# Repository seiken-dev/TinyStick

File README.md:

# TinyStick

**TinyStick**は、**ATtiny3217**(32KB Flash, 2KB SRAM, 256B EEPROM)を搭載した、Arduino互換の開発キットです。消費電流は約4.5mA(クロック10MHz。スリープ時は0.1mA未満)と小さく、コイン電池で長期間動作します。プログラムの書き込みは、付属の**USBシリアル変換基板**(CH340E搭載)で行います。詳しくは、 [tinystick.jp](https://www.tinystick.jp)をご覧ください。

# コンテンツ
- **Arduino**<br>
PlatformIOでビルドできるデモのソースコードです。
- **KiCad**<br>
[KiCad](https://www.kicad.org/)(7.0)のプロジェクトです。TinyStick本体の**TS_Core.kicad_pro**と、USBシリアル変換基板の**TS_USB.kicad_pro**が含まれます。
- **schematic**<br>
TinyStick本体とUSBシリアル変換基板の回路図PDFです。
- **Blender**<br>
3Dプリントケース作成用のBlenderのプロジェクトファイルと、発注に使用したSTLファイルです。

# プログラミング
**TinyStick**のプログラミングは、[PlatformIO](https://platformio.org/)で行います。[Arduino IDE](https://www.arduino.cc/en/software)は、2.3版ではTinyAVR用のボードマネージャーの定義が読み込めない等の理由で推奨しません。(→[参考](https://ameblo.jp/pta55/entry-12835016734.html))

### ビルド
- **PlatformIO**のプロジェクトフォルダに**Arduino**以下をコピーし、適当な名前(例:TinyStickDemo)に変更します。
- **PlatformIO**の**Home**画面から[**Open Project...**]で、このプロジェクトを開きます。
- 必要なplatform(**Atmel megaAVR**)のインストールが自動的に始まります。
- インストールが完了したら**Build**してください。

### UPDI書き込み
- USBシリアル変換基板をUSBケーブルで接続して、スイッチをオンします(赤いLEDが光ります)。このとき、ドライバを自動認識しない場合は、[メーカーのHP](https://wch-ic.com/search?q=CH340&t=downloads)からCH340のドライバをダウンロードしてインストールしてください。
- Windowsの場合は、デバイスマネージャの「ポート(COMとLPT)」に「USB-SERIAL CH340 (COMxx)」と表示されれば完了です。
- **PlatformIO**の**Upload**をクリックすると、プログラムを転送します。

### シリアルデバッグ
- 横のボタン(**Button5**)を押して「Bounce Ball」デモに切り替えたあと、**PlatformIO**の**Serial Monitor**または**Tera Term**等のターミナルアプリを起動すると、加速度の数値が流れてきます。
- このUSBシリアル変換基板は、ターミナルアプリを起動するとRTS信号がLOWになることを利用して、UPDI書き込みとシリアル通信モードを自動的に切り替えます。(Windowsで確認 →[参考](https://ehbtj.com/electronics/make-serial-updi-programmer/))

### platformio.ini
プロジェクトのルートにある設定ファイルです。重要な項目について説明します。

`board_build.f_cpu = 10000000`<br>
CPUクロックを設定します。初期値は10MHz、最大は20MHzです。必ず5の倍数にしてください。そうしないとシリアル通信が文字化けします。また5MHzにすると、I2Cが正常に動作しません。記述しないと16MHzになります。

### ソースコード
- **main.cpp**<br>
メインプログラムで、初期化、タイトル表示、サイドボタン(**Button5**)によるデモの切り替え、長押しによるバックライトのオンオフを処理します。

- **TinyStickDef.h**<br>
共通の#define、ピン定義です。

- **TinyStick.h .cpp**<br>
ボタン、圧電ブザーのクラス、スリープ関連のグローバル関数です。

- **TinyLCD.h .cpp**<br>
バックライト付きLCD [**AQM1248A**](https://akizukidenshi.com/catalog/g/g110048/)に、ビットマップまたは文字を表示するクラスです。文字は、拡大・ボールド・白黒反転・縦・プロポーショナル表示に対応しています。

- **font8x8.h**<br>
8x8ドットフォントです。0x20から0x7Fまでの英数記号です。

- **TinyApp.h .cpp**<br>
複数のアプリを切り替えるときは、このクラスの派生クラスを作成して**main.cpp**に定義するだけで、サイドボタン(**Button5**)で切り替えられます。

- **I2Cbase.h .cpp**<br>
本体内蔵の加速度センサ(**LIS2DH12**)と、M5StickC用のENV Hat(**SHT30**)の基底クラスです。

- **octave.h**<br>
ドレミの周波数を定義したファイルです。

- **playDigit.h .cpp**<br>
２桁の整数値をドレミの音程で鳴らす関数です。

- **app/**<br>
6つのデモアプリです。**TinyApp**の派生クラスです。
  - **EnvHat.h .cpp**<br>
  **ENV Hat**で温度/湿度を表示します。**Button1**で次のアプリに切り替えます。装着されていないときはスキップします。

  - **KitchenTimer.h .cpp**<br>
  キッチンタイマーです。最大99分。スタートすると、分をEEPROMに保存します。

  - **AccelDemo.h .cpp**<br>
  加速度センサのデモです。傾けると玉が転がります。

  - **FontTest.h .cpp**<br>
  8x8ドットフォントをダンプします。**Button1**で拡大、**Button2,3**でスクロールします。

  - **Tetris.h .cpp**<br>
  お馴染みのゲームで、縦向きで遊びます。

  - **Maze3D.h .cpp**<br>
  Line関数を利用した3次元迷路です。

### スリープ機能
一定時間のスリープが出来ます。いずれかのボタンを押すと、スリープから復帰します。
- 時間は任意の時間ではなく、**TinyStick.h**の`enum SleepTime`の時間しか設定できません。
- 本来PX2,PX6ピンに接続されたボタン(TinyStickではButton1のみ)でしかスリープからの復帰はできませんが、これは**FALLING**モードの場合で、**LOW**モードならどのボタンでも復帰が可能です。このため、**LOW**モードでスリープし、起きたら**FALLING**モードに変更して、連続して割り込みが入らないようにしています。

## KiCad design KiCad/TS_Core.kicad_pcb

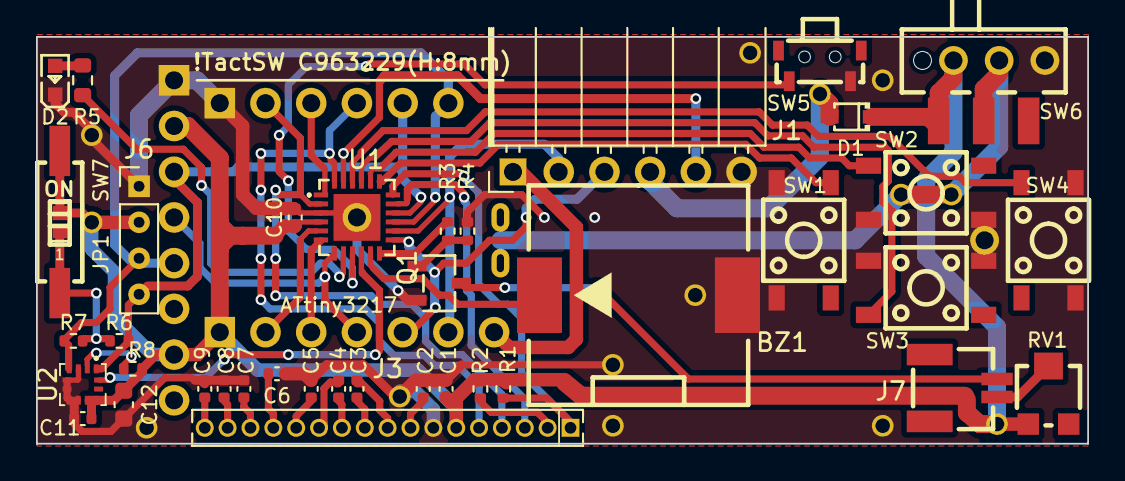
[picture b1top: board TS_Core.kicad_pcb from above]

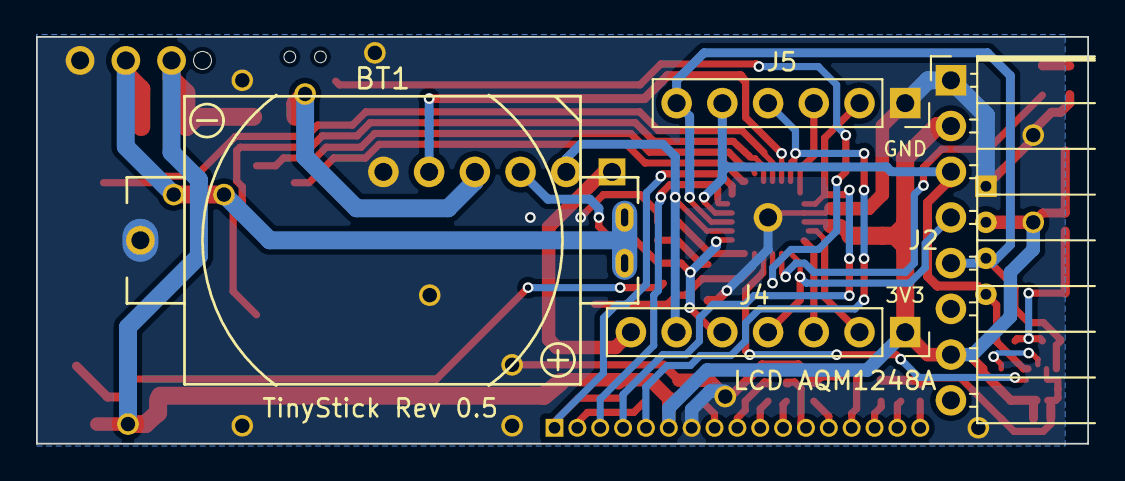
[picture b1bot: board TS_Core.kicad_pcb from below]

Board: 2 copper layers, 58.4 x 22.6 mm, 43 parts (4 on the bottom side), 44 nets.

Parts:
BT1: CR2032; BAT-CR2032-2
BZ1: PKLCS1212E2000; BUZ-SMD_2P-L12.0-W12.0-L
C1, C2, C3, C4, C5, C6, C7, C8, C9: 1u; C_0402_1005Metric
C10, C11: 0.1u; C_0402_1005Metric
C12: 10u; C_0603_1608Metric
D1: 1N5819WS; SOD-323_L1.8-W1.3-LS2.5-RD
D2: SML-D12P8WT86; LED0603-RD_GREEN
J1: USB Serial
J2: M5StickC Hat; PinSocket_M5StickHat
J3: AQM1248A
J4: TinyStick_Ext1; PinSocket_1x07_P2.54mm_Vertical
J5: TinyStick_Ext2; PinSocket_1x06_P2.54mm_Vertical
J6: Grove Connector; Grove_Connector
J7: LCD BackLight; CONN-SMD_HC-1.0-2PWT
JP1: SolderJumper_2_Open; SolderJumper-2_Open_mini
Q1: AO3400A
R1, R2, R6, R7, R8: 10K; R_0402_1005Metric
R3: 20K; R_0402_1005Metric
R4: 100K; R_0402_1005Metric
R5: 470; R_0603_1608Metric
RV1: 2K; RES-ADJ-SMD_G32AT
SW1, SW2, SW3, SW4: Tactile; SW-SMD_4P-L4.5-W4.5-P3.00-LS7.5
SW5: Tactile(Side); SW-SMD_BZCN_TSA002A35
SW6: Slide; SW-SMD_K3-1280S-K1
SW7: DIP; SW-SMD_TSD101EZ
U1: ATtiny3217; HVQFN-24_L4.0-W4.0-P0.50
U2: LIS2DH12; LGA-12_L2.0-W2.0-P0.50-BL

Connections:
+3V3: C1.1, C10.1, C11.1, C12.1, D1.1 (K), J2.2 (5V), J2.7 (3V3), J3.6 (VDD), J4.1, J6.2 (VCC), JP1.2 (B), R1.1, R2.1, R8.1, RV1.3, SW6.1 (A), SW7.2, U1.4 (VCC), U2.9 (Vdd), U2.10 (Vdd_IO)
+5V: J1.1 (+5V), J4.7
Buz: BZ1.1 (-), U1.11 (PB5)
GND: BT1.2 (-), BZ1.2 (+), C1.2, C2.1, C5.1, C6.1, C7.1, C8.1, C9.1, C10.2, C11.2, C12.2, D2.1 (K), J1.6 (GND), J2.1 (GND), J3.7 (VSS), J5.1, J6.1 (GND), Q1.2 (S), R4.2, SW1.3, SW1.4, SW2.3, SW2.4, SW3.3, SW3.4, SW4.3, SW4.4, SW5.2, U1.3 (GND), U1.25 (EP), U2.3 (SA0), U2.5 (RES), U2.6 (GND), U2.7 (GND), U2.8 (GND)
LCD_BL: R3.1, U1.12 (PB4)
LCD_CS: J3.1 (/CS1B), R1.2, U1.18 (PC1)
LCD_RS: J3.3 (RS), U1.17 (PC0)
LED: R5.1, U1.8 (PA7)
MISO: J5.3, U1.1 (PA2/MISO)
MOSI: J3.5 (SDA), J5.4, U1.24 (PA1/MOSI)
unnamed: BT1.1 (+), SW6.2 (B)
unnamed: D1.2 (A), J1.4 (3V3)
unnamed: D2.2 (A), R5.2
unnamed: C3.2, J3.10 (C1+)
unnamed: C3.1, J3.9 (C1-)
unnamed: C4.2, J3.11 (C2+)
unnamed: C4.1, J3.12 (C2-)
unnamed: C9.2, J3.17 (V0)
unnamed: C5.2, J3.13 (V1)
unnamed: C6.2, J3.14 (V2)
unnamed: C7.2, J3.15 (V3)
unnamed: C8.2, J3.16 (V4)
unnamed: C2.2, J3.8 (VOUT)
unnamed: J3.2 (/RST), R2.2
unnamed: J7.1 (LCD_BL_A), RV1.2
unnamed: J7.2 (LCD_BL_K), Q1.3 (D)
unnamed: JP1.1 (A), R6.1, R7.1, SW7.1
unnamed: Q1.1 (G), R3.2, R4.1
unnamed: R8.2, U2.2 (CS)
PA4: J4.2, U1.5 (PA4/SS)
PA5: J4.3, U1.6 (PA5)
PA6: J2.4 (G36/G25), J4.4, U1.7 (PA6)
PB6: U1.10 (PB6), U2.12 (INT1)
RXD: J1.3 (TXD), J4.5, U1.13 (PB3/RXD)
SCK: J3.4 (SCL), J5.2, U1.2 (PA3/SCK)
SCL: J2.3 (G26), J5.5, J6.4 (SCL), R6.2, U1.16 (PB0/SCL), U2.1 (SCL)
SDA: J2.5 (G0), J5.6, J6.3 (SDA), R7.2, U1.15 (PB1/SDA), U2.4 (SDA)
SW1: SW1.1, SW1.2, U1.19 (PC2)
SW2: SW2.1, SW2.2, U1.20 (PC3)
SW3: SW3.1, SW3.2, U1.21 (PC4)
SW4: SW4.1, SW4.2, U1.22 (PC5)
SW5: SW5.1, U1.9 (PB7)
TXD: J1.2 (RXD), J4.6, U1.14 (PB2/TXD)
UPDI: J1.5 (UPDI), U1.23 (PA0/UPDI)

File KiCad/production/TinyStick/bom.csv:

Designator,Footprint,Quantity,Value,LCSC Part #
"_16, _15, _14, _13, _12, _11, _10, _9, _8, _7, _6, _5, _4, _3, _2, ",,16,,
BT1,BAT-CR2032-2,1,CR2032,
BZ1,BUZ-SMD_2P-L12.0-W12.0-L,1,PKLCS1212E2000,C184513
"C1, C2, C3, C4, C5, C6, C7, C8, C9",0402,9,1u,C52923
"C10, C11",0402,2,0.1u,C1525
C12,0603,1,10u,C19702
D1,SOD-323_L1.8-W1.3-LS2.5-RD,1,1N5819WS,C191023
D2,LED0603-RD_GREEN,1,SML-D12P8WT86,C510026
J3,AQM1248A,1,AQM1248A,
J4,PinSocket_1x07_P2.54mm_Vertical,1,TinyStick_Ext1,
J5,PinSocket_1x06_P2.54mm_Vertical,1,TinyStick_Ext2,
J6,Grove_Connector,1,Grove Connector,
J7,CONN-SMD_HC-1.0-2PWT,1,LCD BackLight,C2845361
JP1,SolderJumper-2_Open_mini,1,SolderJumper_2_Open,
Q1,AO3400A,1,AO3400A,C20917
"R1, R2, R6, R7, R8",0402,5,10K,C25744
R3,0402,1,20K,C25765
R4,0402,1,100K,C25741
R5,0603,1,470,C23179
RV1,RES-ADJ-SMD_G32AT,1,2K,C128118
"SW1, SW2, SW3, SW4",SW-SMD_4P-L4.5-W4.5-P3.00-LS7.5,4,Tactile,C963229
SW5,SW-SMD_BZCN_TSA002A35,1,Tactile(Side),C2846757
SW6,SW-SMD_K3-1280S-K1,1,Slide,C128953
SW7,SW-SMD_TSD101EZ,1,DIP,C2758180
U1,HVQFN-24_L4.0-W4.0-P0.50,1,ATtiny3217,C1340454
U2,LGA-12_L2.0-W2.0-P0.50-BL,1,LIS2DH12,C110926

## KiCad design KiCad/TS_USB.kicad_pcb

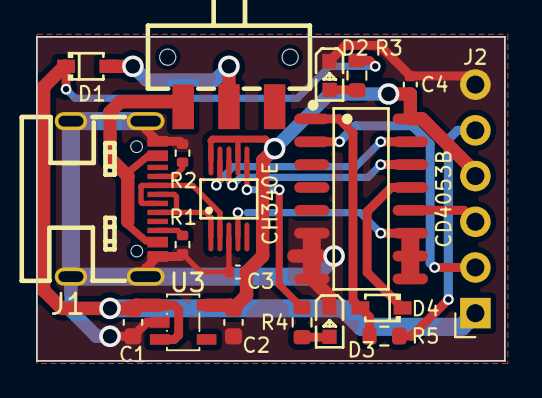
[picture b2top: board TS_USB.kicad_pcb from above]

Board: 2 copper layers, 26.0 x 18.0 mm, 19 parts (0 on the bottom side), 20 nets.

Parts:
C1, C2: 10u; C_0603_1608Metric
C3, C4: 0.1u; C_0402_1005Metric
CD4053B: CD4053B; SOIC-16_L9.9-W3.9-P1.27-LS6.0
CH340E: CH340E; MSOP-10_L3.0-W3.0-P0.50-LS5.0
D1: NSR0320MW2T1G; SOD-323_L1.8-W1.3-LS2.5-RD
D2, D3: LED; LED0603-RD_GREEN
D4: 1N5819WS; SOD-323_L1.8-W1.3-LS2.5-RD
J1: USB_C_Receptacle_USB2.0; USB-C-SMD_TYPE-C-16P-1
J2: Conn_01x06_Pin; PinHeader_1x06_P2.54mm
R1, R2: 5.1K; R_0402_1005Metric
R3: 2.7K; R_0603_1608Metric
R4, R5: 470; R_0603_1608Metric
SW1: Slide; SW-SMD_SSSS211603
U3: ME6217C33; SOT-23-5_L3.0-W1.7-P0.95-LS2.8

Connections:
+3V3: C2.1, C3.1, C4.1, CD4053B.16 (VDD), CH340E.7 (VCC), CH340E.10 (V3), J2.4 (3V3), U3.5 (VOUT)
+5V: C1.1, D1.1 (K), J2.1 (+5V), R3.1, U3.1 (VIN), U3.3 (CE)
GND: C1.2, C2.2, C3.2, C4.2, CD4053B.6 (INH), CD4053B.7 (VEE), CD4053B.8 (VSS), CH340E.3 (GND), D2.1 (K), D3.1 (K), J1.A1B12 (GND), J1.B1A12 (GND), J1.EP, J2.6 (GND), R1.2, R2.2, U3.2 (GND)
unnamed: D1.2 (A), SW1.2 (B)
unnamed: D2.2 (A), R3.2
unnamed: D3.2 (A), R4.2
unnamed: CD4053B.1 (b1), D4.2 (A), R5.2
unnamed: CD4053B.13 (a1), D4.1 (K)
unnamed: J1.A5 (CC1), R2.1
unnamed: J1.B5 (CC2), R1.1
unnamed: CD4053B.2 (b0), J2.2 (RXD)
unnamed: CD4053B.12 (a0), J2.3 (TXD)
unnamed: J2.5 (UPDI), R5.1
unnamed: J1.A4B9 (VBUS), J1.B4A9 (VBUS), SW1.1 (A)
unnamed: CD4053B.15 (B), CH340E.9 (RXD)
unnamed: CH340E.6 (TNOW), R4.1
unnamed: CD4053B.14 (A), CH340E.8 (TXD)
unnamed: CH340E.1 (UD+), J1.A6 (D+), J1.B6 (D+)
unnamed: CH340E.2 (UD-), J1.A7 (D-), J1.B7 (D-)
unnamed: CD4053B.9 (SC), CD4053B.10 (SB), CD4053B.11 (SA), CH340E.4 (~RTS)

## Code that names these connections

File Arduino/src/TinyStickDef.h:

#pragma once

#define DEBUG_SERIAL

#define BUTTONS_COUNT 5

#define TS_SLEEP // sleep support
#define LCD_VERTICAL // vertical mode
#define LCD_TEXT_PROP // proportional
#define LCD_DRAW_LINE

//#define PLAY_DIGIT // play digit by tone
#define USE_EEPROM // save settings in EEPROM

#define EEPROM_KITCHEN_TIMER_MINUTE 1

#define PIN_LED PIN_PA7
#define PIN_BUZZER PIN_PB5

#define PIN_LCD_RS PIN_PC0
#define PIN_LCD_CS PIN_PC1
#define PIN_LCD_BL PIN_PB4

#define PIN_BUTTON1 PIN_PC2
#define PIN_BUTTON2 PIN_PC3
#ifdef ARDUINO_attinyxy7
  #define PIN_BUTTON3 PIN_PC4
  #define PIN_BUTTON4 PIN_PC5
#else
  #define PIN_BUTTON3 PIN_PB4
  #define PIN_BUTTON4 PIN_PB5
#endif

#if (BUTTONS_COUNT == 5)
  #define btnSide btn5
  #ifdef ARDUINO_attinyxy7
    #define PIN_BUTTON5 PIN_PB7
  #else
    #define PIN_BUTTON5 PIN_PA5
  #endif
#else
  #define btnSide btn4
#endif

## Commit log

2024-08-22 update 5 buttons
2024-08-22 modify README.md
2025-11-14 remove unused variable and redefine elapse in loop function
2025-11-14 Initial plan
2025-11-14 Change elapse variable type to uint32_t for cross-platform consistency
2025-11-14 fix: remove unused variable and adjust elapse calculation in loop.
